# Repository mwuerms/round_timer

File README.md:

# round_timer

a small round timer, watch, 

## Ideas

* minumum
    * timer (alarm)
        * multiple at the same time
    * simple to use
    * nice sounds, like from mp3, ogg, ...
    * runs from battery (LiPo or similar)
    * round display, GUI
* also nice
    * watch
    * sensors like humidity, pressure, temperatur, light, magnetic (compass), ...
    * vibra for alarm

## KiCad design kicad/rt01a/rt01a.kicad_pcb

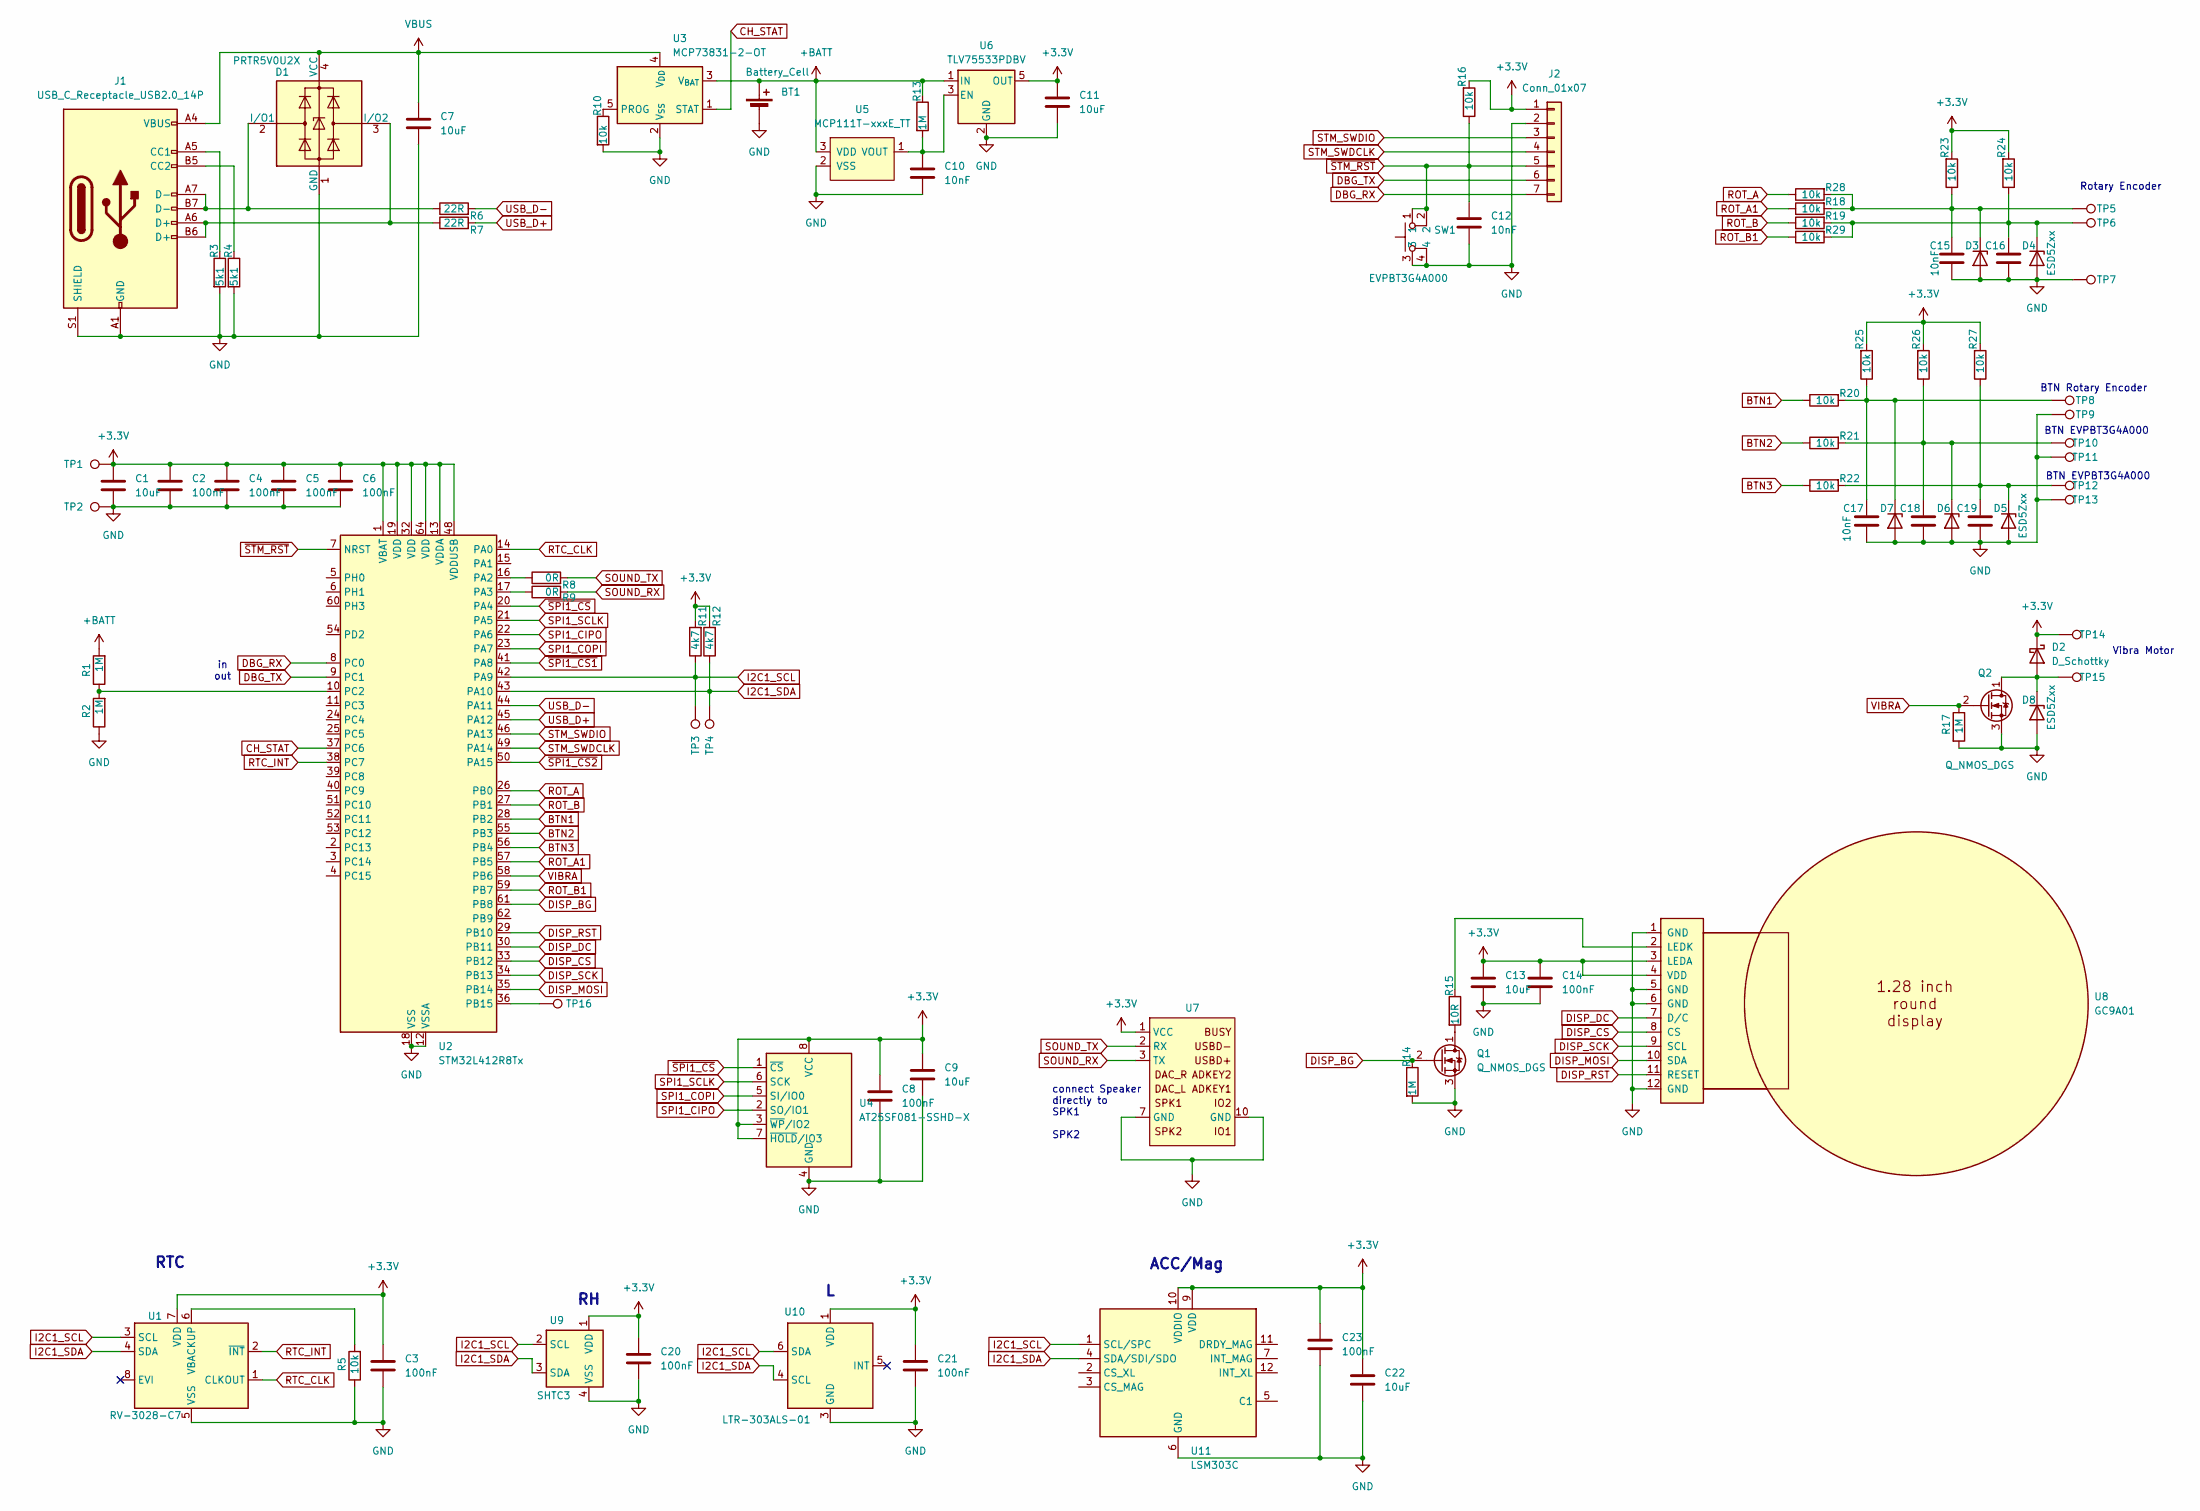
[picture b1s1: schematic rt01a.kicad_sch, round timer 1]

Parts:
BT1: Battery_Cell; PinHeader_1x02_P2.54mm_Vertical
C1, C7, C9, C11, C13, C22: 10uF; C_0805_2012Metric_Pad1.18x1.45mm_HandSolder
C2, C3, C4, C5, C6, C8, C14, C20, C21, C23: 100nF; C_0603_1608Metric_Pad1.08x0.95mm_HandSolder
C10, C12, C15, C16, C17, C18, C19: 10nF; C_0603_1608Metric_Pad1.08x0.95mm_HandSolder
D1: PRTR5V0U2X; SOT-143
D2: D_Schottky; D_SOD-523
D3, D4, D5, D6, D7, D8: ESD5Zxx; D_SMF
J1: USB_C_Receptacle_USB2.0_14P; USB_C_Receptacle_GCT_USB4110
J2: Conn_01x07; PinHeader_1x07_P1.27mm_Vertical
Q1, Q2: Q_NMOS_DGS; SOT-23-3
R1, R2, R13, R14, R17: 1M; R_0603_1608Metric_Pad0.98x0.95mm_HandSolder
R3, R4: 5k1; R_0603_1608Metric_Pad0.98x0.95mm_HandSolder
R5, R10, R16, R18, R19, R20, R21, R22, R23, R24, R25, R26, R27, R28, R29: 10k; R_0603_1608Metric_Pad0.98x0.95mm_HandSolder
R6, R7: 22R; R_0603_1608Metric_Pad0.98x0.95mm_HandSolder
R8, R9: 0R; R_0603_1608Metric_Pad0.98x0.95mm_HandSolder
R11, R12: 4k7; R_0603_1608Metric_Pad0.98x0.95mm_HandSolder
R15: 10R; R_0603_1608Metric_Pad0.98x0.95mm_HandSolder
SW1: EVPBT3G4A000; EVPBT3
TP1, TP2, TP3, TP4, TP5, TP6, TP7, TP8, TP9, TP10, TP11, TP12, TP13, TP14, TP15, TP16: TestPoint; TestPoint_Pad_D1.0mm
U1: RV-3028-C7; MicroCrystal_C7_SON-8_1.5x3.2mm_P0.9mm
U2: STM32L412R8Tx; LQFP-64_10x10mm_P0.5mm
U3: MCP73831-2-OT; SOT-23-5
U4: AT25SF081-SSHD-X; SOIC-8_3.9x4.9mm_P1.27mm
U5: MCP111T-xxxE_TT; SOT-23-3
U6: TLV75533PDBV; SOT-23-5
U7: DFPlayer_Mini-TF-16P_Minimal
U8: GC9A01; FP-128HR01A
U9: SHTC3; Sensirion_DFN-4-1EP_2x2mm_P1mm_EP0.7x1.6mm
U10: LTR-303ALS-01; Lite-On_LTR-303ALS-01
U11: LSM303C; LGA-12_2x2mm_P0.5mm

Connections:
+3.3V: C1.1, C2.1, C3.1, C4.1, C5.1, C6.1, C8.1, C9.1, C11.1, C13.1, C14.1, C20.1, C21.1, C22.1, C23.1, D2.1 (K), J2.1, R11.2, R12.2, R16.2, R23.2, R24.2, R25.2, R26.2, R27.2, TP1.1, TP14.1, U1.7 (VDD), U2.1 (VBAT), U2.13 (VDDA), U2.19 (VDD), U2.32 (VDD), U2.48 (VDDUSB), U2.64 (VDD), U4.3 (~WP/IO2), U4.7 (~HOLD/IO3), U4.8 (VCC), U6.5 (OUT), U7.1 (VCC), U8.3 (LEDA), U8.4 (VDD), U9.1 (VDD), U10.1 (VDD), U11.9 (VDD), U11.10 (VDDIO)
+BATT: BT1.1 (+), R1.2, R13.1, U3.3 (V_{BAT}), U5.3 (VDD), U6.1 (IN)
BTN1: R20.1, U2.28 (PB2)
BTN2: R21.1, U2.55 (PB3)
BTN3: R22.1, U2.56 (PB4)
CH_STAT: U2.37 (PC6), U3.1 (STAT)
DBG_RX: J2.7, U2.8 (PC0)
DBG_TX: J2.6, U2.9 (PC1)
DISP_BG: Q1.2 (G), R14.1, U2.61 (PB8)
DISP_CS: U2.33 (PB12), U8.8 (CS)
DISP_DC: U2.30 (PB11), U8.7 (D/C)
DISP_MOSI: U2.35 (PB14), U8.10 (SDA)
DISP_RST: U2.29 (PB10), U8.11 (RESET)
DISP_SCK: U2.34 (PB13), U8.9 (SCL)
GND: BT1.2 (-), C1.2, C2.2, C3.2, C4.2, C5.2, C6.2, C7.2, C8.2, C9.2, C10.2, C11.2, C12.2, C13.2, C14.2, C15.2, C16.2, C17.2, C18.2, C19.2, C20.2, C21.2, C22.2, C23.2, D1.1 (GND), D3.2 (A), D4.2 (A), D5.2 (A), D6.2 (A), D7.2 (A), D8.2 (A), J1.A1 (GND), J1.A12 (GND), J1.B1 (GND), J1.B12 (GND), J1.S1 (SHIELD), J2.2, Q1.3 (S), Q2.3 (S), R2.1, R3.2, R4.2, R5.1, R10.2, R14.2, R17.2, SW1.3, SW1.4, TP2.1, TP7.1, TP9.1, TP11.1, TP13.1, U1.5 (VSS), U2.12 (VSSA), U2.18 (VSS), U2.31 (VSS), U2.47 (VSS), U2.63 (VSS), U3.2 (V_{SS}), U4.4 (GND), U5.2 (VSS), U6.2 (GND), U7.7 (GND), U7.10 (GND), U8.1 (GND), U8.5 (GND), U8.6 (GND), U8.12 (GND), U9.4 (VSS), U10.3 (GND), U11.6 (GND), U11.8 (GND)
I2C1_SCL: R11.1, TP3.1, U1.3 (SCL), U2.42 (PA9), U9.2 (SCL), U10.6 (SDA), U11.1 (SCL/SPC)
I2C1_SDA: R12.1, TP4.1, U1.4 (SDA), U2.43 (PA10), U9.3 (SDA), U10.4 (SCL), U11.4 (SDA/SDI/SDO)
unnamed: D1.2 (I/O1), J1.A7 (D-), J1.B7 (D-), R6.1
unnamed: D1.3 (I/O2), J1.A6 (D+), J1.B6 (D+), R7.1
unnamed: D2.2 (A), D8.1 (K), Q2.1 (D), TP15.1
unnamed: C15.1, D3.1 (K), R18.2, R23.1, R28.2, TP5.1
unnamed: C16.1, D4.1 (K), R19.2, R24.1, R29.2, TP6.1
unnamed: C19.1, D5.1 (K), R22.2, R27.1, TP12.1
unnamed: C18.1, D6.1 (K), R21.2, R26.1, TP10.1
unnamed: C17.1, D7.1 (K), R20.2, R25.1, TP8.1
unnamed: J1.A5 (CC1), R3.1
unnamed: J1.B5 (CC2), R4.1
unnamed: Q1.1 (D), R15.2
unnamed: R5.2, U1.6 (VBACKUP)
unnamed: R8.1, U2.16 (PA2)
unnamed: R9.1, U2.17 (PA3)
unnamed: TP16.1, U2.36 (PB15)
unnamed: R1.1, R2.2, U2.10 (PC2)
unnamed: R10.1, U3.5 (PROG)
unnamed: C10.1, R13.2, U5.1 (VOUT), U6.3 (EN)
unnamed: R15.1, U8.2 (LEDK)
ROT_A: R28.1, U2.26 (PB0)
ROT_A1: R18.1, U2.57 (PB5)
ROT_B: R19.1, U2.27 (PB1)
ROT_B1: R29.1, U2.59 (PB7)
RTC_CLK: U1.1 (CLKOUT), U2.14 (PA0)
RTC_INT: U1.2 (~INT), U2.38 (PC7)
SOUND_RX: R9.2, U7.3 (TX)
SOUND_TX: R8.2, U7.2 (RX)
SPI1_CIPO: U2.22 (PA6), U4.2 (SO/IO1)
SPI1_COPI: U2.23 (PA7), U4.5 (SI/IO0)
SPI1_SCLK: U2.21 (PA5), U4.6 (SCK)
STM_SWDCLK: J2.4, U2.49 (PA14)
STM_SWDIO: J2.3, U2.46 (PA13)
USB_D+: R7.2, U2.45 (PA12)
USB_D-: R6.2, U2.44 (PA11)
VBUS: C7.1, D1.4 (VCC), J1.A4 (VBUS), J1.A9 (VBUS), J1.B4 (VBUS), J1.B9 (VBUS), U3.4 (V_{DD})
VIBRA: Q2.2 (G), R17.1, U2.58 (PB6)
~SPI1_CS1: U2.41 (PA8)
~SPI1_CS2: U2.50 (PA15)
~SPI1_CS: U2.20 (PA4), U4.1 (~CS)
~STM_RST: C12.1, J2.5, R16.1, SW1.1, SW1.2, U2.7 (NRST)

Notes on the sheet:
BTN EVPBT3G4A000
Rotary Encoder
RTC
connect Speaker directly to SPK1 SPK2
Vibra Motor
BTN Rotary Encoder
ACC/Mag
in out

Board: 4 copper layers, 93 parts (85 on the bottom side), 55 nets, no tracks yet.

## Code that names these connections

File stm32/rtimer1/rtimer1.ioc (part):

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Mcu.Name=STM32L412R8Tx
Mcu.Package=LQFP64
Mcu.UserName=STM32L412R8Tx
PA0.GPIOParameters=GPIO_Label
PA0.GPIO_Label=RTC_CLK
PA0.Signal=S_TIM2_ETR
PA13\ (JTMS/SWDIO).Mode=Serial_Wire
PA13\ (JTMS/SWDIO).Signal=SYS_JTMS-SWDIO
PA14\ (JTCK/SWCLK).Mode=Serial_Wire
PA14\ (JTCK/SWCLK).Signal=SYS_JTCK-SWCLK
PA2.GPIOParameters=GPIO_Label
PA2.GPIO_Label=SOUND_TX
PA2.Mode=Asynchronous
PA2.Signal=USART2_TX
PA3.GPIOParameters=GPIO_Label
PA3.GPIO_Label=SOUND_RX
PA3.Mode=Asynchronous
PA3.Signal=USART2_RX
PB0.GPIOParameters=GPIO_Label
PB0.GPIO_Label=ROT_A
PB0.Signal=GPXTI0
PB1.GPIOParameters=GPIO_Label
PB1.GPIO_Label=ROT_B
PB1.Signal=GPXTI1
PB10.GPIOParameters=GPIO_Label
PB10.GPIO_Label=DISP_RST
PB10.Signal=GPIO_Output
PB11.GPIOParameters=GPIO_Label
PB11.GPIO_Label=DISP_DC
PB11.Signal=GPIO_Output
PB12.GPIOParameters=GPIO_Label
PB12.GPIO_Label=DISP_CS
PB12.Signal=GPIO_Output
PB13.GPIOParameters=GPIO_Label
PB13.GPIO_Label=DISP_SCK
PB13.Mode=Full_Duplex_Master
PB13.Signal=SPI2_SCK
PB14.GPIOParameters=GPIO_Label
PB14.GPIO_Label=DISP_MISO
PB14.Mode=Full_Duplex_Master
PB14.Signal=SPI2_MISO
PB15.GPIOParameters=GPIO_Label
PB15.GPIO_Label=DISP_MOSI
PB15.Mode=Full_Duplex_Master
PB15.Signal=SPI2_MOSI
PB2.GPIOParameters=GPIO_Label
PB2.GPIO_Label=BTN1
PB2.Signal=GPXTI2
PB3\ (JTDO/TRACESWO).GPIOParameters=GPIO_Label
PB3\ (JTDO/TRACESWO).GPIO_Label=BTN2
PB3\ (JTDO/TRACESWO).Signal=GPXTI3
PB4\ (NJTRST).GPIOParameters=GPIO_Label
PB4\ (NJTRST).GPIO_Label=BTN3
PB4\ (NJTRST).Signal=GPXTI4
PB5.GPIOParameters=GPIO_Label
PB5.GPIO_Label=ENC_IN1
PB5.Mode=Encoder_mode_occur1
PB5.Signal=LPTIM1_IN1
PB6.GPIOParameters=GPIO_Label
PB6.GPIO_Label=VIBRA
PB6.Signal=GPIO_Output
PB7.GPIOParameters=GPIO_Label
PB7.GPIO_Label=ENC_IN2
PB7.Mode=Encoder_mode_occur1
PB7.Signal=LPTIM1_IN2
PB8.Signal=S_TIM16_CH1
PC0.GPIOParameters=GPIO_Label
PC0.GPIO_Label=DBG_RX
PC0.Mode=Asynchronous
PC0.Signal=LPUART1_RX
PC1.GPIOParameters=GPIO_Label
PC1.GPIO_Label=DBG_TX
PC1.Mode=Asynchronous
PC1.Signal=LPUART1_TX
PC2.GPIOParameters=GPIO_Label
PC2.GPIO_Label=BAT
PC2.Signal=ADCx_IN3
PC6.GPIOParameters=GPIO_Label
PC6.GPIO_Label=CH_STAT
PC6.Signal=GPXTI6
PC7.GPIOParameters=GPIO_Label
PC7.GPIO_Label=RTC_INT
PC7.Signal=GPXTI7
RCC.HSE_VALUE=8000000
RCC.SYSCLKFreq_VALUE=16000000
RCC.SYSCLKSource=RCC_SYSCLKSOURCE_HSI
board=custom

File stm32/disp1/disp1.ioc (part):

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Mcu.Name=STM32L412RBTxP
Mcu.Package=LQFP64
Mcu.UserName=STM32L412RBTxP
PA10.Mode=I2C
PA10.Signal=I2C1_SDA
PA13\ (JTMS/SWDIO).Mode=Serial_Wire
PA13\ (JTMS/SWDIO).Signal=SYS_JTMS-SWDIO
PA14\ (JTCK/SWCLK).Mode=Serial_Wire
PA14\ (JTCK/SWCLK).Signal=SYS_JTCK-SWCLK
PA2.GPIOParameters=GPIO_Label
PA2.GPIO_Label=SOUND_TX
PA2.Mode=Asynchronous
PA2.Signal=USART2_TX
PA3.GPIOParameters=GPIO_Label
PA3.GPIO_Label=SOUND_RX
PA3.Mode=Asynchronous
PA3.Signal=USART2_RX
PA9.Mode=I2C
PA9.Signal=I2C1_SCL
PB10.GPIOParameters=GPIO_Label
PB10.GPIO_Label=DISP_RST
PB10.Signal=GPIO_Output
PB11.GPIOParameters=GPIO_Label
PB11.GPIO_Label=DISP_DC
PB11.Signal=GPIO_Output
PB12.GPIOParameters=GPIO_Label
PB12.GPIO_Label=DISP_CS
PB12.Signal=GPIO_Output
PB13.GPIOParameters=GPIO_Label
PB13.GPIO_Label=DISP_SCK
PB13.Mode=Full_Duplex_Master
PB13.Signal=SPI2_SCK
PB14.GPIOParameters=GPIO_Label
PB14.GPIO_Label=DISP_MISO
PB14.Mode=Full_Duplex_Master
PB14.Signal=SPI2_MISO
PB15.GPIOParameters=GPIO_Label
PB15.GPIO_Label=DISP_MOSI
PB15.Mode=Full_Duplex_Master
PB15.Signal=SPI2_MOSI
PB3\ (JTDO/TRACESWO).GPIOParameters=GPIO_PuPd,GPIO_Label,GPIO_ModeDefaultEXTI
PB3\ (JTDO/TRACESWO).GPIO_Label=BTN2
PB3\ (JTDO/TRACESWO).GPIO_ModeDefaultEXTI=GPIO_MODE_IT_RISING_FALLING
PB3\ (JTDO/TRACESWO).GPIO_PuPd=GPIO_PULLUP
PB3\ (JTDO/TRACESWO).Signal=GPXTI3
PB4\ (NJTRST).GPIOParameters=GPIO_PuPd,GPIO_Label,GPIO_ModeDefaultEXTI
PB4\ (NJTRST).GPIO_Label=BTN1
PB4\ (NJTRST).GPIO_ModeDefaultEXTI=GPIO_MODE_IT_RISING_FALLING
PB4\ (NJTRST).GPIO_PuPd=GPIO_PULLUP
PB4\ (NJTRST).Signal=GPXTI4
PB5.GPIOParameters=GPIO_PuPd,GPIO_Label,GPIO_ModeDefaultEXTI
PB5.GPIO_Label=ENC_A
PB5.GPIO_ModeDefaultEXTI=GPIO_MODE_IT_RISING_FALLING
PB5.GPIO_PuPd=GPIO_PULLUP
PB5.Signal=GPXTI5
PB6.GPIOParameters=GPIO_PuPd,GPIO_Label,GPIO_ModeDefaultEXTI
PB6.GPIO_Label=BTN0
PB6.GPIO_ModeDefaultEXTI=GPIO_MODE_IT_RISING_FALLING
PB6.GPIO_PuPd=GPIO_PULLUP
PB6.Signal=GPXTI6
PB7.GPIOParameters=GPIO_PuPd,GPIO_Label,GPIO_ModeDefaultEXTI
PB7.GPIO_Label=ENC_B
PB7.GPIO_ModeDefaultEXTI=GPIO_MODE_IT_RISING_FALLING
PB7.GPIO_PuPd=GPIO_PULLUP
PB7.Signal=GPXTI7
PC10.GPIOParameters=GPIO_Label
PC10.GPIO_Label=DBG0
PC10.Signal=GPIO_Output
PC11.GPIOParameters=GPIO_Label
PC11.GPIO_Label=DBG1
PC11.Signal=GPIO_Output
RCC.HSE_VALUE=8000000
RCC.SYSCLKFreq_VALUE=16000000
RCC.SYSCLKSource=RCC_SYSCLKSOURCE_HSI
board=custom

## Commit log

2025-02-10 added round 1.28 inch display
2025-02-10 dfplayer added
2025-02-10 speaker added
2025-02-10 rotary encoder added
    from manufacturer
    https://bourns.com/resources/design-tools/engineering-files-list?Folder=PER60
2025-02-10 round_timer01 added, 1st try out
2025-02-10 rotary encoder added, gitignore added
2025-02-10 tryout 1
2025-02-10 usbc USB4110 added
2025-02-10 PEC11S added
2025-02-10 mockup1
2025-02-11 mockup 1, case top part, 3d print
2025-02-12 part speaker, new part added, therefore renamed
2025-02-12 case mockup2, top case done
2025-02-12 mockup case 2
2025-02-12 button added
2025-02-13 new parts added
2025-02-13 new parts added, place new button
2025-02-14 case 03
2025-02-16 started kicad tr01a project
2025-02-16 removed rt01a_1, _2, not needed anymore
2025-02-16 rt01a added footprint, some placements done
2025-02-21 case 4
2025-02-23 schematics seems done
2025-02-23 rtimer1 stm32cubeide project started, pindefinitions
2025-02-23 added disp
2025-02-26 stm32 disp, testing project added
2025-02-26 testing disp1
2025-02-26 disp1: 1st simple input routines
2025-02-26 disp1 mmscheduler added
2025-02-26 disp1: sending events from usr_in to app works
2025-02-28 LPTM2 as timer works, event timer works, sending events to app works
2025-03-03 disp1 tinkered in events, but not done yet
2025-03-03 rtimer02 started FreeRTOS project
2025-03-05 rtimer02 added user input, gui funcs to draw onto display
2025-03-13 rtimer02 1st version of timer_app display, all there but not yet very good
2025-03-13 rtimer02 display a little better, need larger font for number "00:00"
2025-03-13 rtimer02 started gui elements
2025-03-13 rtimer02 more gui, looks better
2025-03-16 rtimer02 added progress bar as gui element
2025-03-16 rtimer02 speed up x8 -> no more display flickering + added gui_cursor_side()
